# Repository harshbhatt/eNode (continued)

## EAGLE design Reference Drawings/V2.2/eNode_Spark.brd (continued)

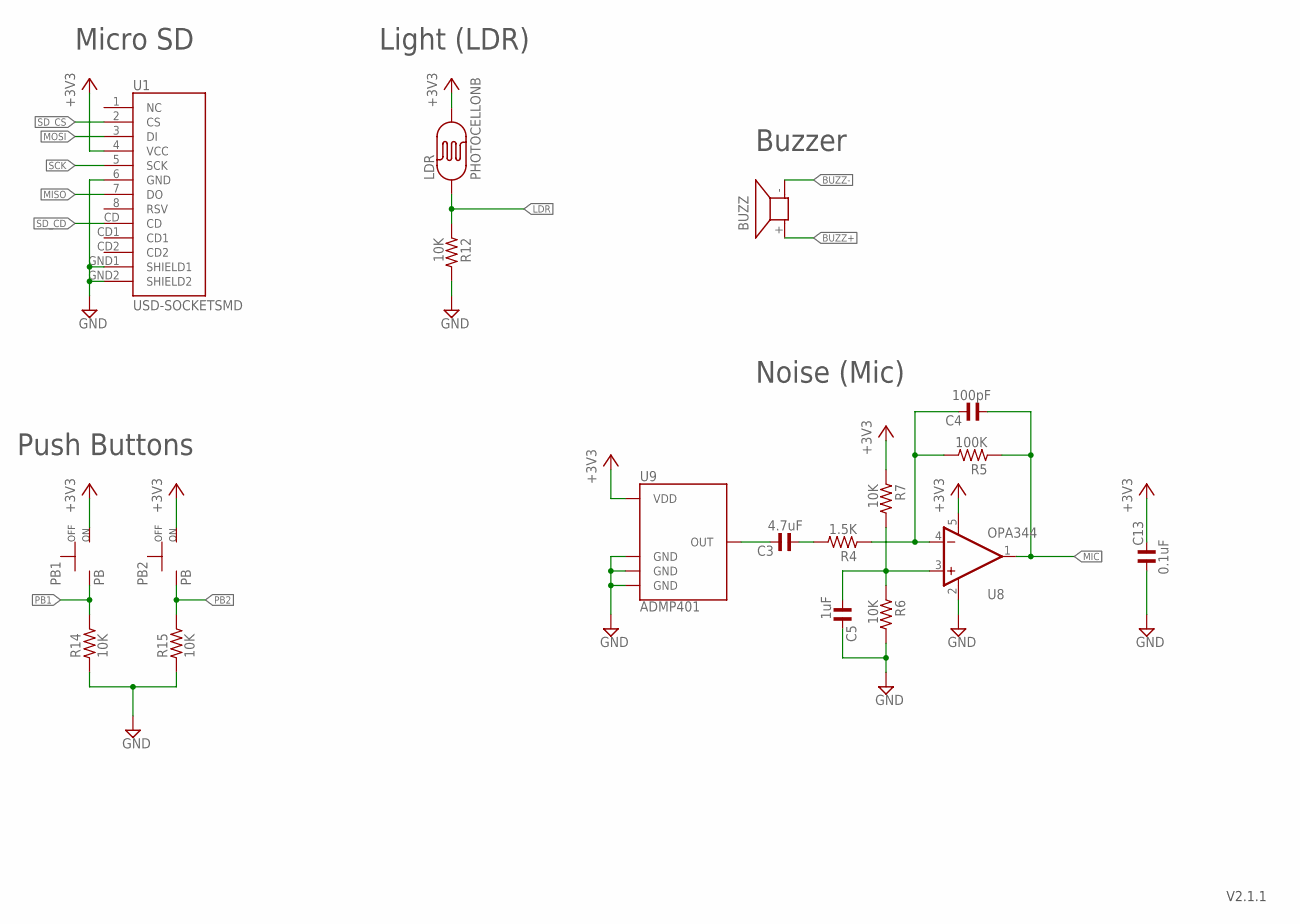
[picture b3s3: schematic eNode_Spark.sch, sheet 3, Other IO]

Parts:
BUZZ: BUZZER; OFFBOARD_NOSIGN
C3: 4.7uF; C0402
C4: 100pF; C0402
C5: 1uF; C0402
C13: 0.1uF; C0402
LDR: PHOTOCELLONB; ON_BOARD
PB1, PB2: PB
R4: 1.5K; R0402
R5: 100K; R0402
R6, R7: 10K; R0402
R12, R14, R15: 10K; R0603
U1: USD-SOCKETSMD; MICRO-SD-SOCKET-PP
U8: OPA344; SOT23-5
U9: ADMP401

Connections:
+3V3: C13.2, LDR.2, PB1.2, PB2.2, R7.1, U1.4 (VCC), U8.5 (V+), U9.5 (VDD); also elsewhere on the board
BUZZ+: BUZZ.+; also elsewhere on the board
BUZZ-: BUZZ.-; also elsewhere on the board
GND: C5.2, C13.1, R6.2, R12.2, R14.1, R15.1, U1.6 (GND), U1.GND1 (SHIELD1), U1.GND2 (SHIELD2), U8.2 (V-), U9.2 (GND), U9.4 (GND), U9.6 (GND); also elsewhere on the board
LDR: LDR.1, R12.1; also elsewhere on the board
MIC: C4.1, R5.1, U8.1 (OUT); also elsewhere on the board
MISO: U1.7 (DO); also elsewhere on the board
MOSI: U1.3 (DI); also elsewhere on the board
unnamed: C3.2, U9.1 (OUT)
unnamed: C3.1, R4.2
unnamed: C4.2, R4.1, R5.2, U8.4 (-IN)
unnamed: C5.1, R6.1, R7.2, U8.3 (+IN)
PB1: PB1.1, R14.2; also elsewhere on the board
PB2: PB2.1, R15.2; also elsewhere on the board
SCK: U1.5 (SCK); also elsewhere on the board
SD_CD: U1.CD; also elsewhere on the board
SD_CS: U1.2 (CS); also elsewhere on the board

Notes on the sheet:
Micro SD
Push Buttons
Light (LDR)
Buzzer
Noise (Mic)
V2.1.1

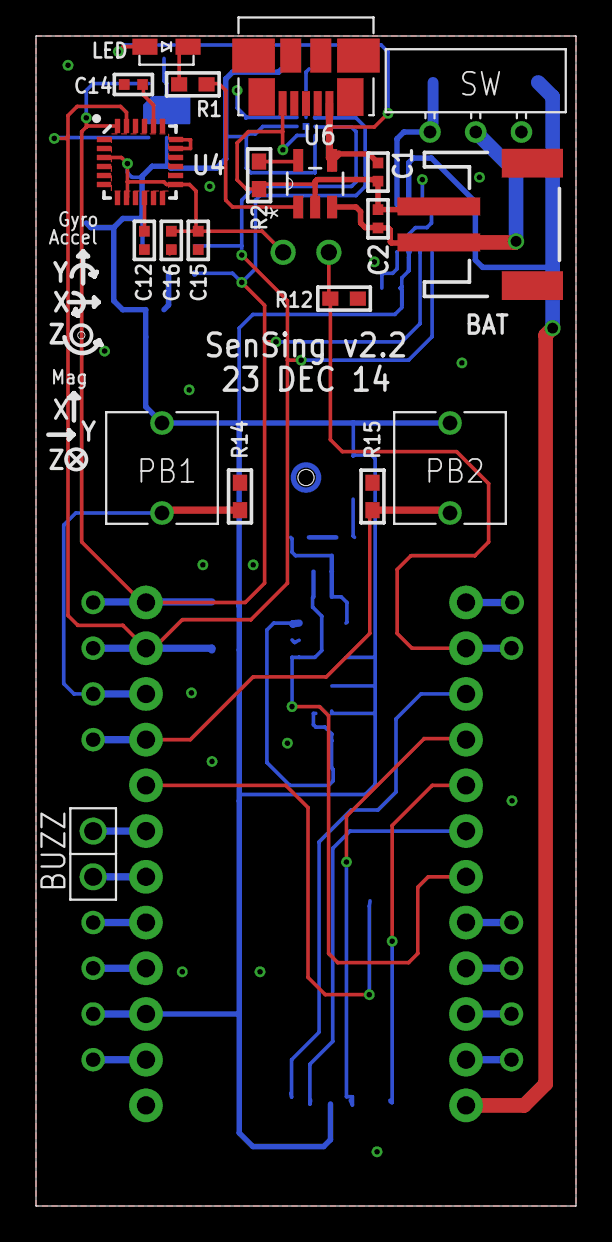
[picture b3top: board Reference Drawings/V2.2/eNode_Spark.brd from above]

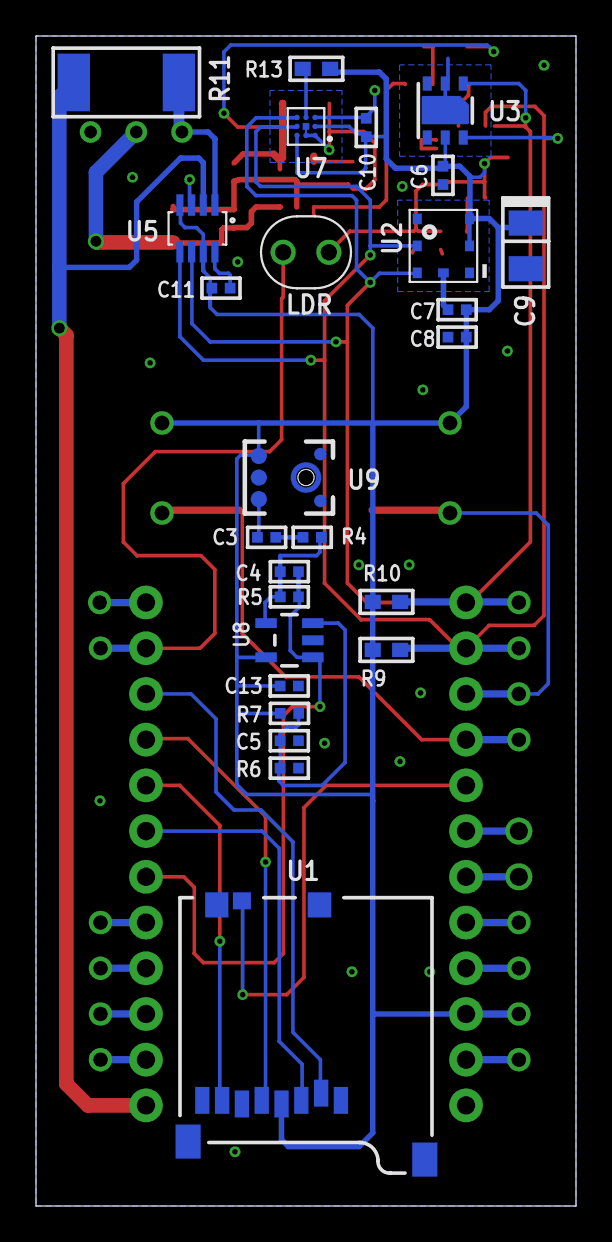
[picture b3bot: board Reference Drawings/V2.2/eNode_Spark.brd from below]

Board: 2 copper layers, 30.0 x 65.0 mm, 61 parts (26 on the bottom side), 35 nets.

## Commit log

2015-02-08 Initial Commit
    Added all files
2015-02-24 Major commit
    Updated rev from 3.0 to 3.1
2015-02-24 Updated Traces
    Updated traces near top of BM-09
2015-02-25 Fully Routed
    Fully Routed, DRC checked, Gerbers generated
